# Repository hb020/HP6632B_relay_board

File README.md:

HP 66332A and HP 6632B-6634B #760 Relay Option Board
===================
This repository contains the schematics for a PCB to mount a relay board in an HP 6632B (and siblings) power supply. It is an adaption of the original A6 PCB used in option #760 units.
This relay board allows 2 things:
- the use of these power supplies as a 4 quadrant "poor man's SMU" (but with relay glitches).
- to isolate the output. In some situations, like with a large capacitive load or a battery, it is possible to damage the PSU's crowbar circuit when switching the output off. This board allows the disconnection of the output terminals. 

It is not needed to recalibrate the device after installation, although it would not hurt.

Once installed, you will NOT see the option appear when requesting `*OPT?` via the control interface (RS232/GPIB) (at least not on firmware 1.03). You will now however be able to use the relay control options in the front panel menu (under Output), or via `OUTPout`, `OUTPut:RELay`, and `OUTPut:RELay:POLarity`.

In contrast to the original option #760 PCB, this board:
- is meant to be used with front binding posts. See [option 020 board](https://github.com/hb020/HP6632B_binding_posts). If you want to use it with the standard backside terminals: just add 4 connections from the top connector to the bottom connector, according to the original schema that can be found in the service manual (the relevant extract can be found [here](doc/66332A%20Service%20Manual_9018-01125_extract.pdf)).
- has other minor changes like swapping the ports on the driver IC and allowing the use of standard series resistors (at least, the series that I had). 
- makes no use of the MP23/06612-00005 "Relay Option Bracket", which you will likely not have anyway if you do not already have the #760 board. The board is small enough and the weight distribution is such that this is not likely to be a problem.

For the component choice I took inspiration from "lukier" on [eevblog](https://www.eevblog.com/forum/repair/agilent-6632b-fault-repair-and-several-design-flaws/msg1019018/#msg1019018). The main difference from his list was the FFC connectivity: 15cm is too short. I used molex 15267-0237: 20cm.

The components and layout chosen allow the board to be used on all variants of the HP 663xB family - even the 100 V 6634B.

The final result looks like this:

Board behaviour
-----
This board keeps the sense lines functional, and I have not seen an impact on accuracy.
The sign of the voltage and current as measured (and set) does not change when you switch to "reverse" mode (the display still continues to show a positive voltage, although the voltage on the terminals is now negative).

During relay switching there are the inevitable delays and small artifacts.
Below is a switch from -1V (Reversed) to +1V (Normal), with a 1MΩ load. The switchover takes a little less than 80ms. 

The sine wave in the middle of the screen is 50Hz mains hum, as during that period the PSU output is disconnected. That hum, and the small spike that follows it, are largely suppressed when a load is applied.

About
-----
The root folder contains the KiCAD files. 
The gerber files can be found in the [/gerber](gerber/) folder.

Documentation of some of the components, and an extract of the service manual, with the original board drawings, can be found in the [/doc](doc/) folder. All files are publicly available on the respective manufacturers's websites, and are copied here for convenience. If this poses problems, let me know.

Related Repositories and info
--------------------

You may want to combine this with the [option 020 Frontpanel Binding Posts](https://github.com/hb020/HP6632B_binding_posts).

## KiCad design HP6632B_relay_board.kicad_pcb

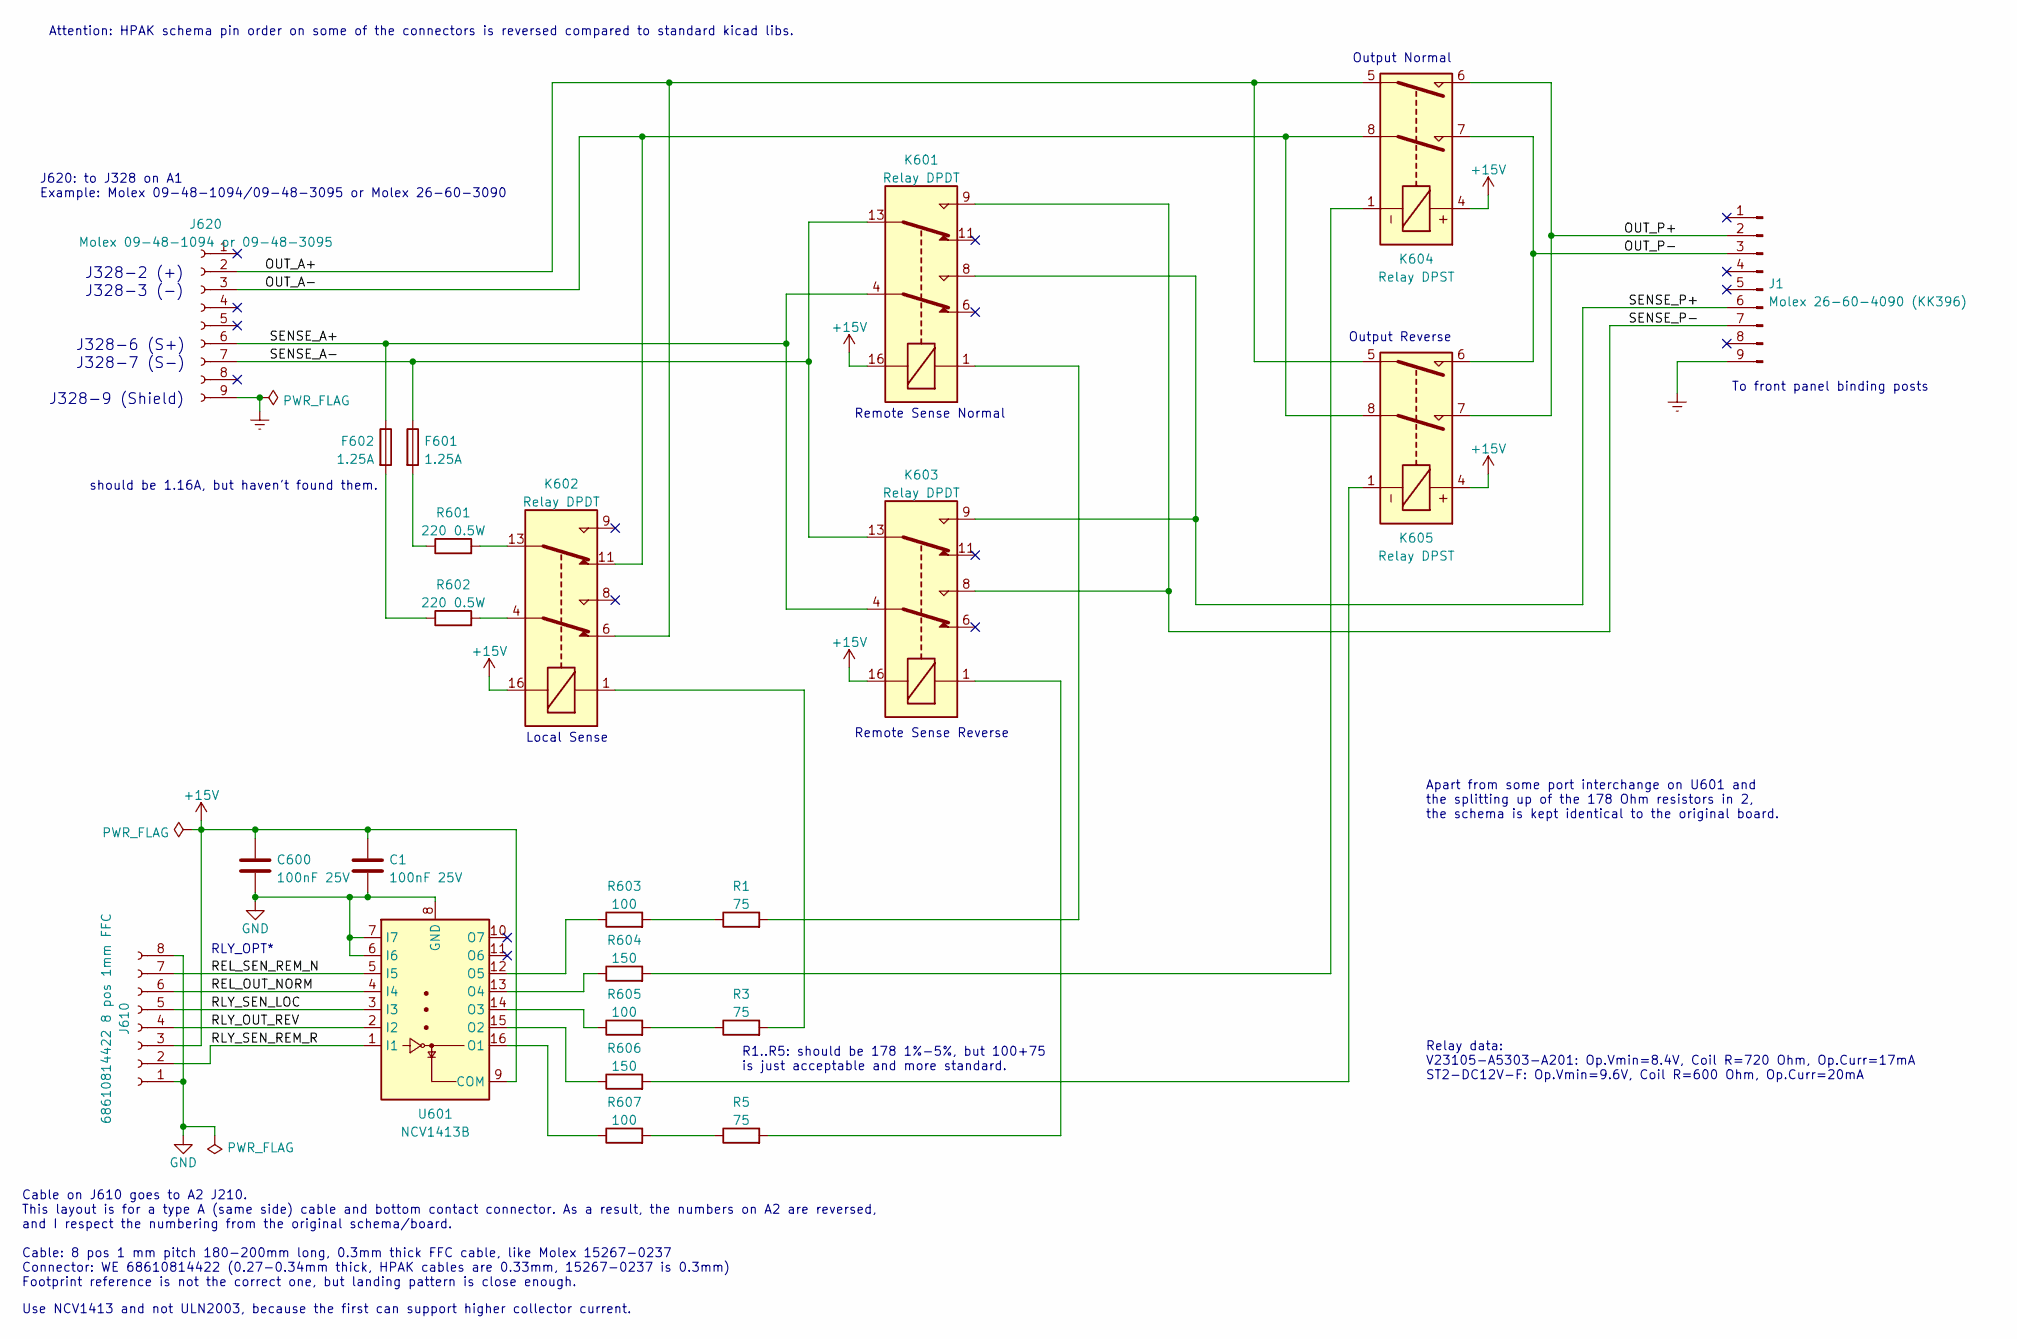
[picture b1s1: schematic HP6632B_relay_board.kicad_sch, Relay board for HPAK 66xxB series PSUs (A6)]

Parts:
C1, C600: 100nF 25V; C_0805_2012Metric_Pad1.18x1.45mm_HandSolder
F601, F602: 1.25A; Fuse_Littelfuse_395Series
J1: Molex 26-60-4090 (KK396); Molex_KK-396_A-41791-0009_1x09_P3.96mm_Vertical
J610: 68610814422 8 pos 1mm FFC; TE_84953-8_1x08-1MP_P1.0mm_Horizontal
J620: Molex 09-48-1094 or 09-48-3095; Molex_KK-396_A-41815-0009_1x09_P3.96mm_Horizontal
K601, K602, K603: Relay DPDT; Relay_DPDT_Omron_G5V-2
K604, K605: Relay DPST; Relay_Panasonic_ST2-F
R1, R3, R5: 75; R_1206_3216Metric_Pad1.30x1.75mm_HandSolder
R601, R602: 220 0.5W; R_1206_3216Metric_Pad1.30x1.75mm_HandSolder
R603, R605, R607: 100; R_1206_3216Metric_Pad1.30x1.75mm_HandSolder
R604, R606: 150; R_1206_3216Metric_Pad1.30x1.75mm_HandSolder
U601: NCV1413B; SOIC-16_3.9x9.9mm_P1.27mm

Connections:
+15V: C1.1, C600.1, J610.3, K601.16, K602.16, K603.16, K604.4, K605.4, U601.9 (COM)
/OUT_A+: J620.2, K602.6, K604.5, K605.5
/OUT_A-: J620.3, K602.11, K604.8, K605.8
/OUT_P+: J1.2, K604.6, K605.7
/OUT_P-: J1.3, K604.7, K605.6
/REL_OUT_NORM: J610.6, U601.4 (I4)
/REL_SEN_REM_N: J610.7, U601.5 (I5)
/RLY_OUT_REV: J610.4, U601.2 (I2)
/RLY_SEN_LOC: J610.5, U601.3 (I3)
/RLY_SEN_REM_R: J610.2, U601.1 (I1)
/SENSE_A+: F602.1, J620.6, K601.4, K603.4
/SENSE_A-: F601.1, J620.7, K601.13, K603.13
/SENSE_P+: J1.6, K601.8, K603.9
/SENSE_P-: J1.7, K601.9, K603.8
Earth: J1.9, J620.9
GND: C1.2, C600.2, J610.1, J610.8, U601.6 (I6), U601.7 (I7), U601.8 (GND)
unnamed: F601.2, R601.1
unnamed: F602.2, R602.1
unnamed: K601.1, R1.2
unnamed: K602.1, R3.2
unnamed: K602.4, R602.2
unnamed: K602.13, R601.2
unnamed: K603.1, R5.2
unnamed: K604.1, R604.2
unnamed: K605.1, R606.2
unnamed: R1.1, R603.2
unnamed: R3.1, R605.2
unnamed: R5.1, R607.2
unnamed: R607.1, U601.16 (O1)
unnamed: R606.1, U601.15 (O2)
unnamed: R605.1, U601.14 (O3)
unnamed: R604.1, U601.13 (O4)
unnamed: R603.1, U601.12 (O5)

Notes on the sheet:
Use NCV1413 and not ULN2003, because the first can support higher collector current.
should be 1.16A, but haven't found them.
J328-2 (+)
Output Reverse
R1..R5: should be 178 1%-5%, but 100+75 is just acceptable and more standard.
RLY_OPT*
Attention: HPAK schema pin order on some of the connectors is reversed compared to standard kicad libs.
J328-3 (-)
J620: to J328 on A1 Example: Molex 09-48-1094/09-48-3095 or Molex 26-60-3090
J328-9 (Shield)
Relay data: V23105-A5303-A201: Op.Vmin=8.4V, Coil R=720 Ohm, Op.Curr=17mA ST2-DC12V-F: Op.Vmin=9.6V, Coil R=600 Ohm, Op.Curr=20mA
J328-6 (S+)
Remote Sense Reverse
Cable on J610 goes to A2 J210. This layout is for a type A (same side) cable and bottom contact connector. As a result, the numbers on A2 are reversed, and I respect the numbering from the original schema/board. Cable: 8 pos 1 mm pitch 180-200mm long, 0.3mm thick FFC cable, like Molex 15267-0237 Co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
J328-7 (S-)
Remote Sense Normal
Output Normal
To front panel binding posts
Local Sense
Apart from some port interchange on U601 and the splitting up of the 178 Ohm resistors in 2, the schema is kept identical to the original board.

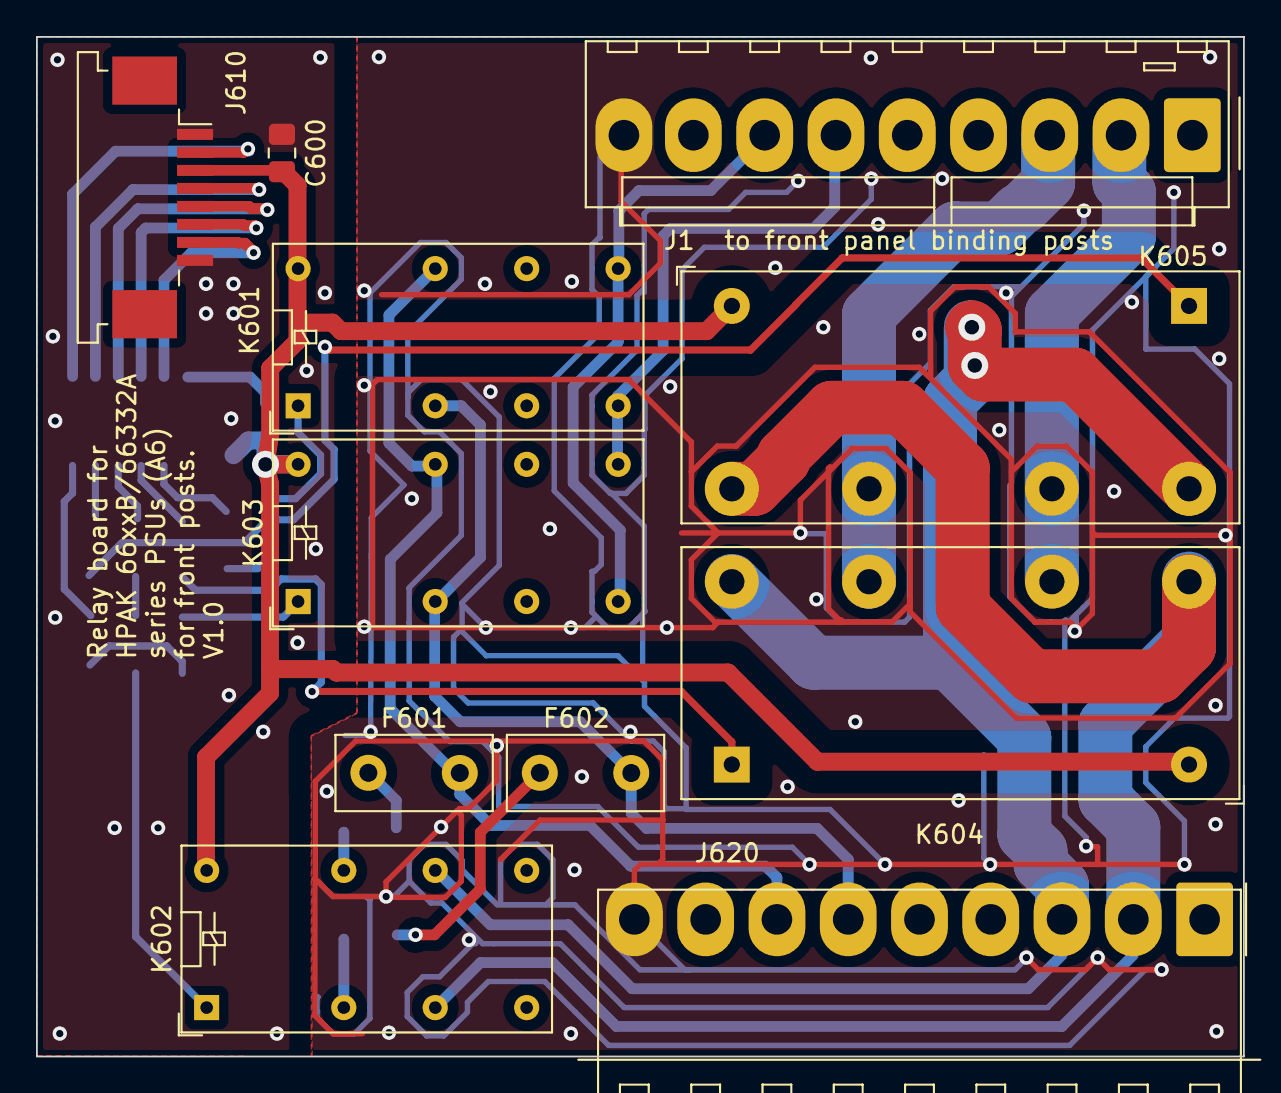
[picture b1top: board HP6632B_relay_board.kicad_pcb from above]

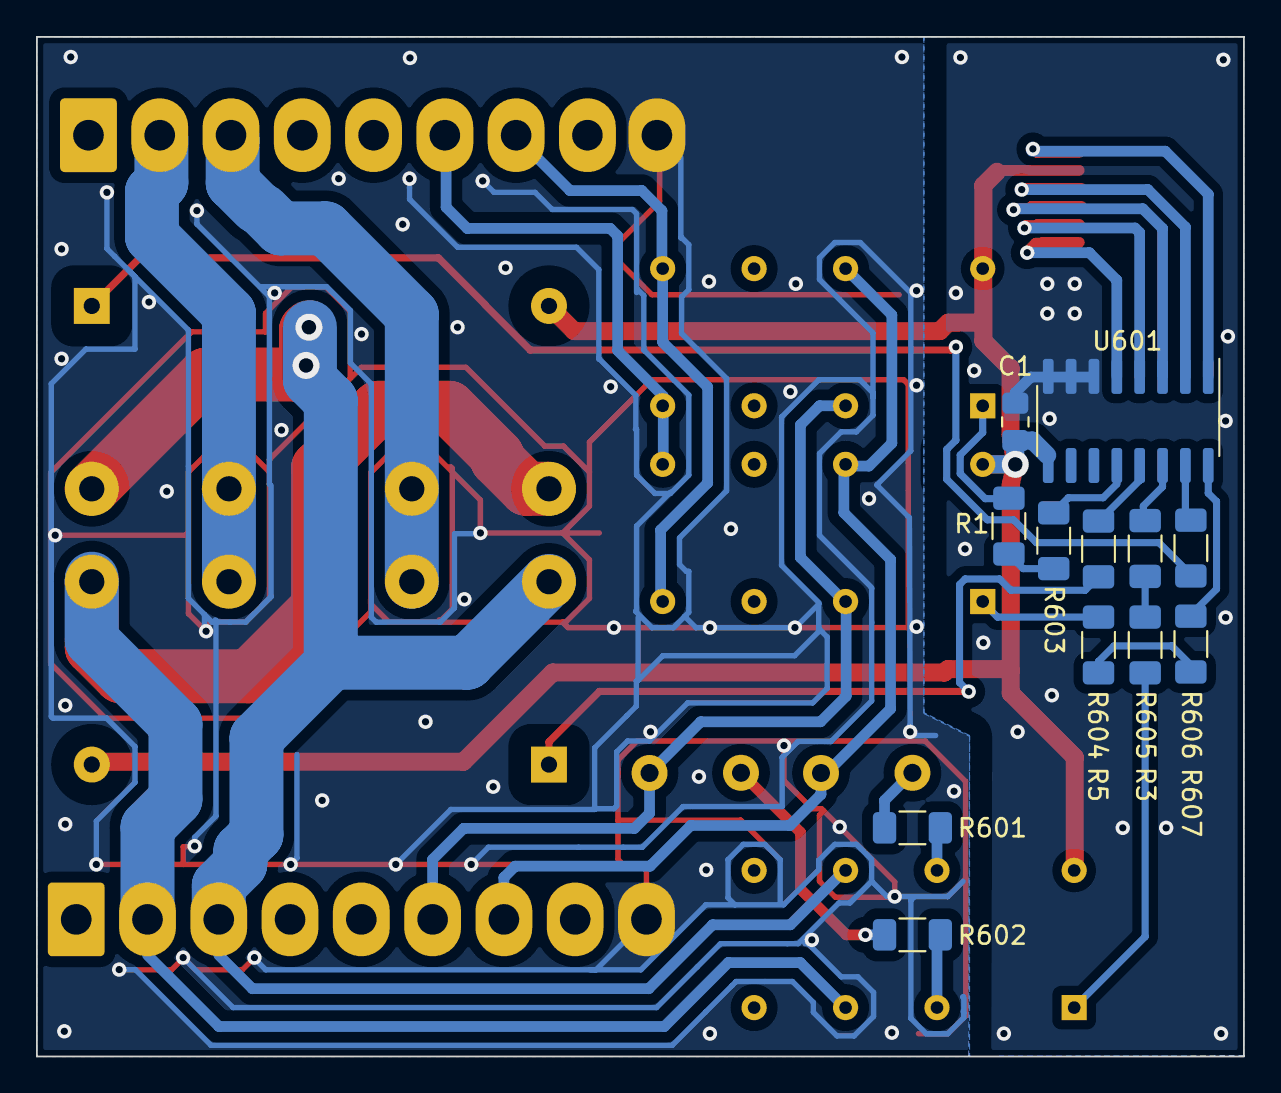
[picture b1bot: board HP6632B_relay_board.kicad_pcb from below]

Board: 2 copper layers, 67.1 x 56.6 mm, 23 parts (12 on the bottom side), 33 nets.

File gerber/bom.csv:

Designator,Footprint,Quantity,Value,LCSC Part #
"C1, C600",C_0805_2012Metric_Pad1.18x1.45mm_HandSolder,2,100nF 25V,
"F601, F602",Fuse_Littelfuse_395Series,2,Bussmann SS-5H-1.25A-APH,
J1,Molex_KK-396_A-41791-0009_1x09_P3.96mm_Vertical,1,Molex 26-60-4090 (KK396),
J610,TE_84953-8_1x08-1MP_P1.0mm_Horizontal,1,68610814422 8 pos 1mm FFC,
J620,Molex_KK-396_A-41815-0009_1x09_P3.96mm_Horizontal,1,Molex 09-48-1094 or 09-48-3095,
"K601, K602, K603",Relay_DPDT_Omron_G5V-2,3,V23105-A5303-A201,
"K604, K605",Relay_Panasonic_ST2-F,2,ST2-DC12V-F,
"R1, R3, R5",R_1206_3216Metric_Pad1.30x1.75mm_HandSolder,3,75,
"R601, R602",R_1206_3216Metric_Pad1.30x1.75mm_HandSolder,2,220 0.5W,
"R603, R605, R607",R_1206_3216Metric_Pad1.30x1.75mm_HandSolder,3,100,
"R604, R606",R_1206_3216Metric_Pad1.30x1.75mm_HandSolder,2,150,
U601,SOIC-16_3.9x9.9mm_P1.27mm,1,NCV1413B,

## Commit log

2022-10-16 publish
2022-10-16 spelling...
2022-10-16 remove stuff to be ignored
2022-10-16 complete ignores
2022-10-16 more documentation
2023-08-08 update to newer kicad version, added interactive BOM
2023-08-08 removed superfluous files
2025-04-02 Update README.md, added FFC cable ref
2025-04-02 Update README.md, FFC length
